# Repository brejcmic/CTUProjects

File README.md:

# CTUProjects
Student and research projects at CTU in Prag

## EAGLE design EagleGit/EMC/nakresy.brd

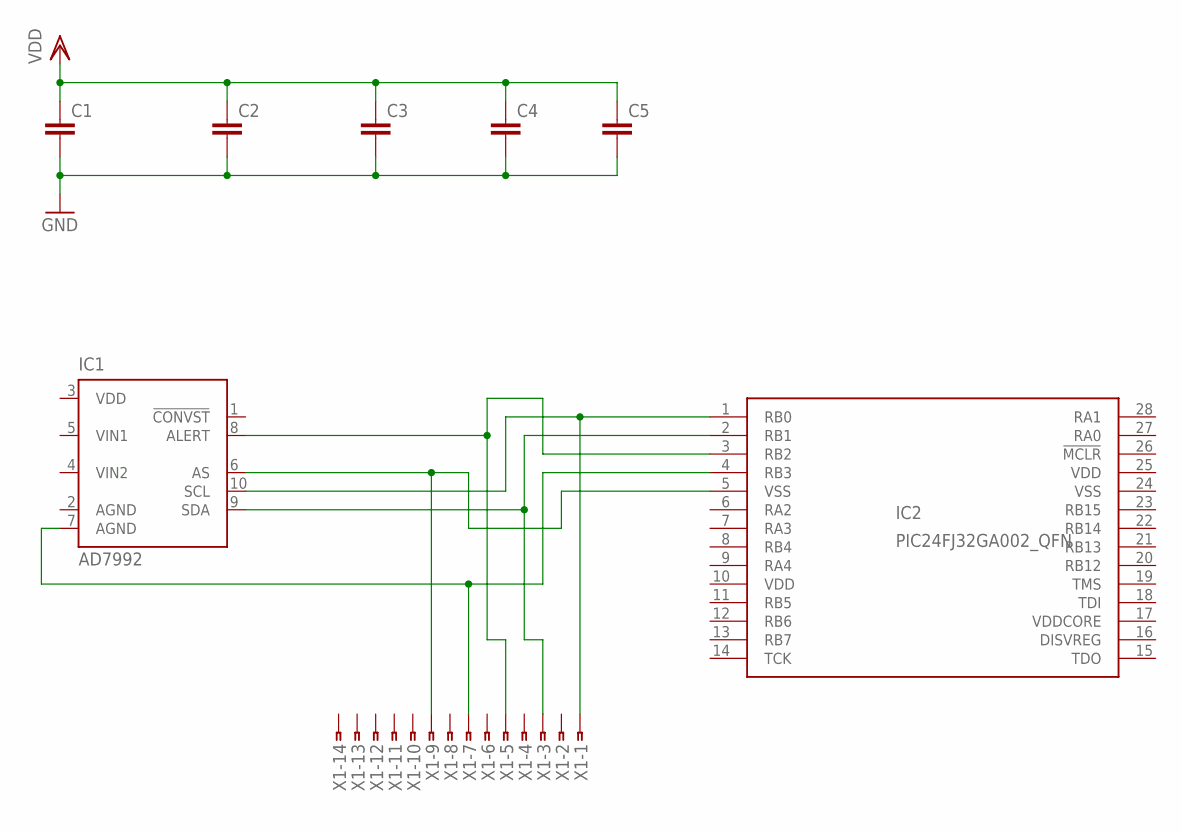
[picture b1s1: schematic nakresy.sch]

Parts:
C1, C2, C3, C4, C5: C-EUC0805K; C0805K
IC1: AD7992; MSOP10
IC2: PIC24FJ32GA002_QFN; QFN28-ML_6X6MM
X1: SMDTOP-14; SMDTOP14

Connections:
AGND: IC1.2 (AGND)
GND: C1.2, C2.2, C3.2, C4.2, C5.2
unnamed: IC1.10 (SCL), IC2.1 (RB0), X1.1
unnamed: IC1.9 (SDA), IC2.2 (RB1), X1.3
unnamed: IC1.8 (ALERT), IC2.3 (RB2), X1.5
unnamed: IC1.7 (AGND), IC2.4 (RB3), X1.7
unnamed: IC1.6 (AS), IC2.5 (VSS), X1.9
VDD: C1.1, C2.1, C3.1, C4.1, C5.1, IC1.3 (VDD), IC2.10 (VDD), IC2.25 (VDD)
VDDCORE: IC2.17 (VDDCORE)
VSS: IC2.24 (VSS)

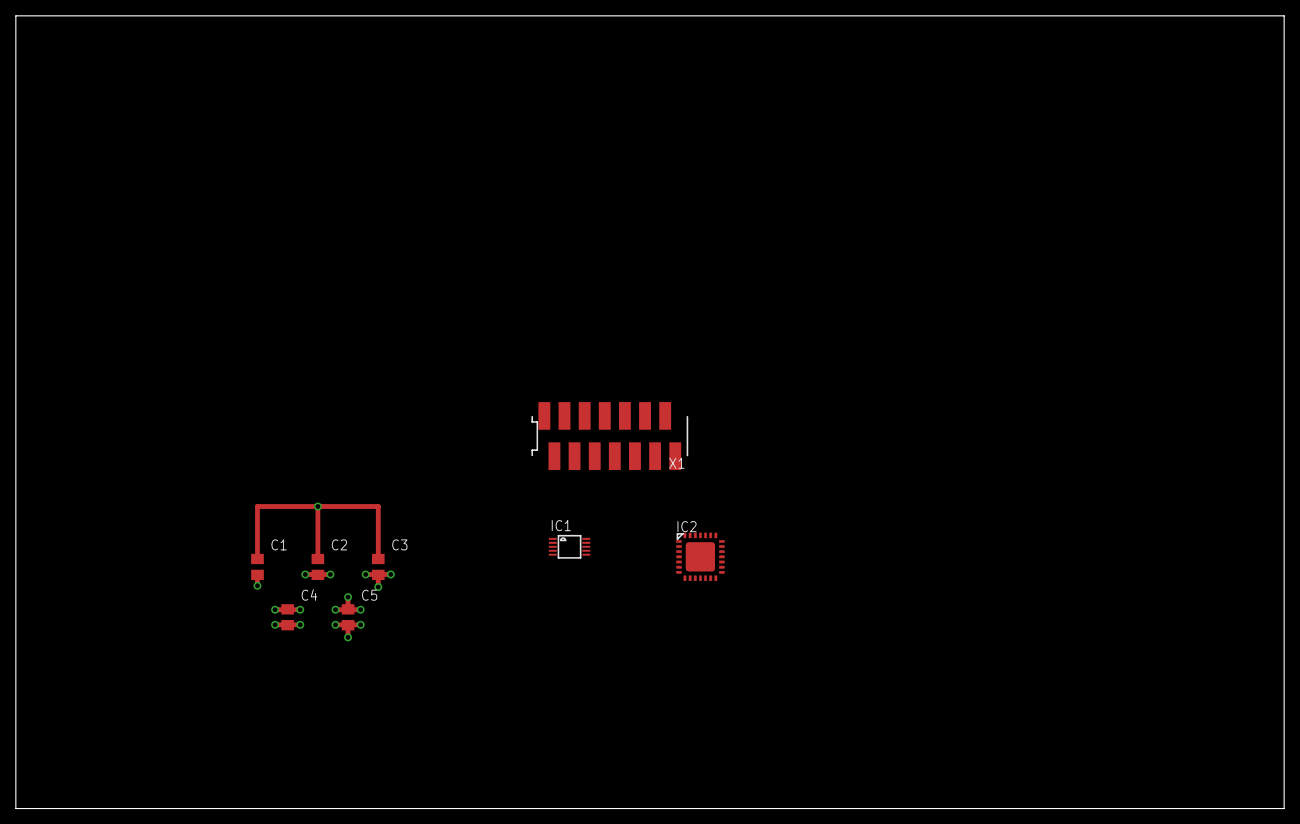
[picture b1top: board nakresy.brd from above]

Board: 4 copper layers, 160.0 x 100.0 mm, 8 parts (0 on the bottom side), 7 nets.

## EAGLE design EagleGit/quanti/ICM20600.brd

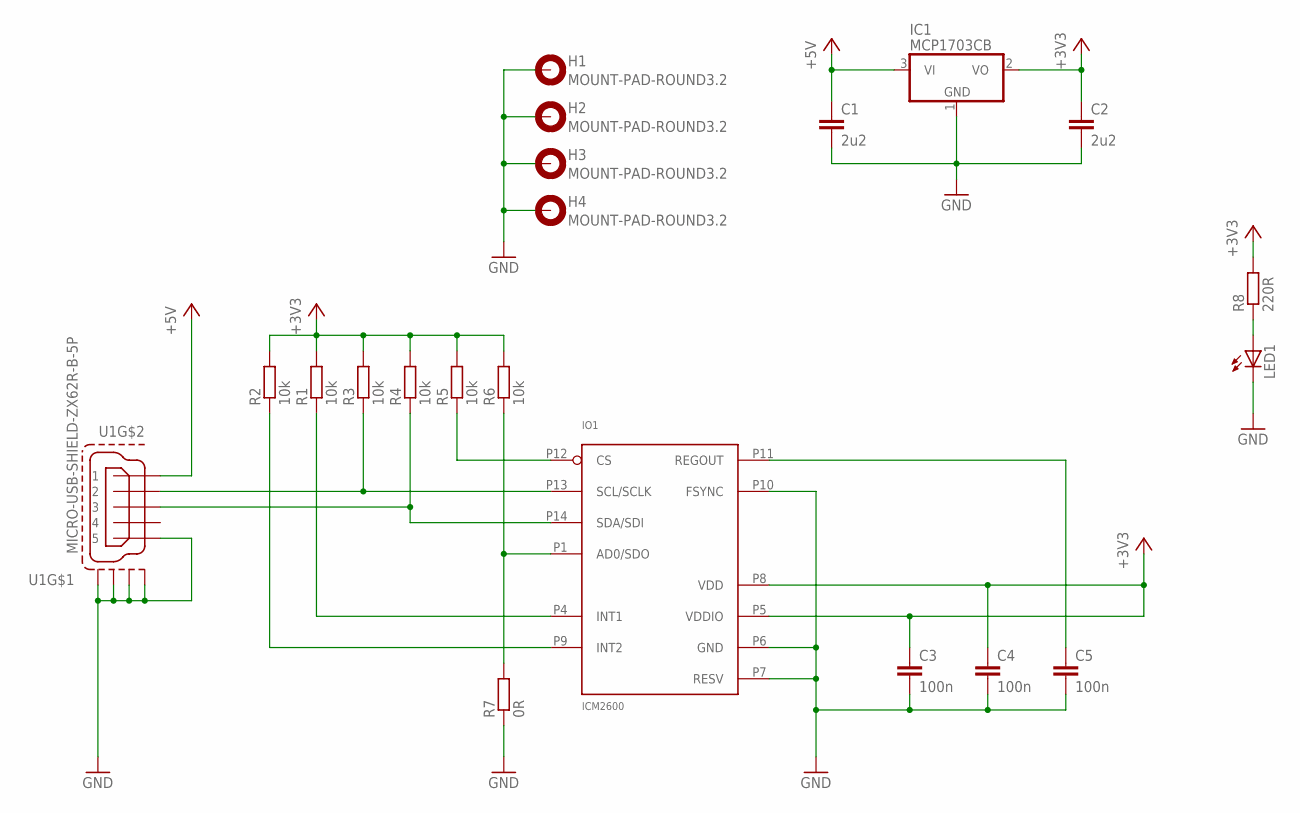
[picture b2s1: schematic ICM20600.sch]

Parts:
C1, C2: 2u2; C0603
C3, C4, C5: 100n; C0603
H1, H2, H3, H4: MOUNT-PAD-ROUND3.2; 3,2-PAD
IC1: MCP1703CB; SOT23
IO1: ICM2600; LGA14
LED1: LEDSML0603; SML0603
R1, R2, R3, R4, R5, R6: 10k; R0603
R7: 0R; R0603
R8: 220R; R0603
U1: MICRO-USB-SHIELD-ZX62R-B-5P; ZX62R-B-5P

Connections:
+3V3: C2.1, C3.1, C4.1, IC1.2 (VO), IO1.P5 (VDDIO), IO1.P8 (VDD), R1.2, R2.2, R3.2, R4.2, R5.2, R6.2, R8.2
+5V: C1.1, IC1.3 (VI), U1.1
GND: C1.2, C2.2, C3.2, C4.2, C5.2, H1.B3,2, H2.B3,2, H3.B3,2, H4.B3,2, IC1.1 (GND), IO1.P6 (GND), IO1.P7 (RESV), IO1.P10 (FSYNC), LED1.C, R7.1, U1.5, U1.M1 (S1), U1.M2 (S2), U1.M3 (S3), U1.M4 (S4)
unnamed: IO1.P9 (INT2), R2.1
unnamed: IO1.P4 (INT1), R1.1
unnamed: C5.1, IO1.P11 (REGOUT)
unnamed: IO1.P13 (SCL/SCLK), R3.1, U1.2
unnamed: IO1.P14 (SDA/SDI), R4.1, U1.3
unnamed: IO1.P12 (CS), R5.1
unnamed: IO1.P1 (AD0/SDO), R6.1, R7.2
unnamed: LED1.A, R8.1

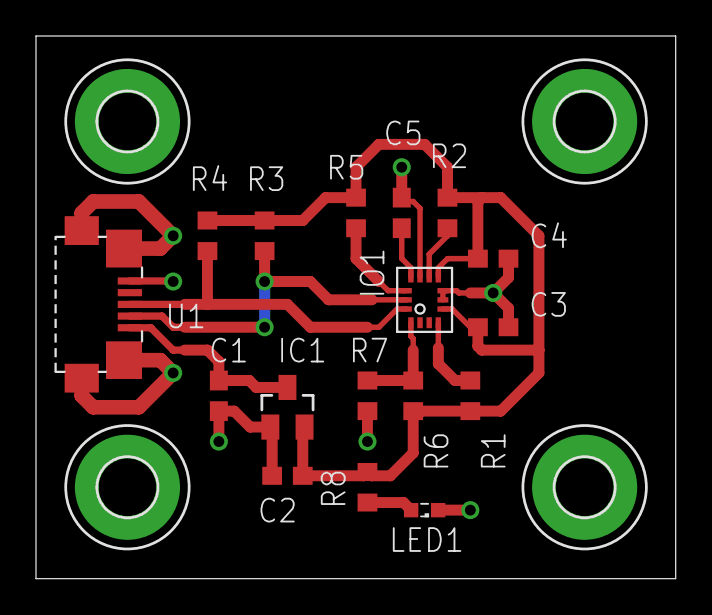
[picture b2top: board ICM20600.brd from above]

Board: 2 copper layers, 35.5 x 30.1 mm, 21 parts (0 on the bottom side), 11 nets.

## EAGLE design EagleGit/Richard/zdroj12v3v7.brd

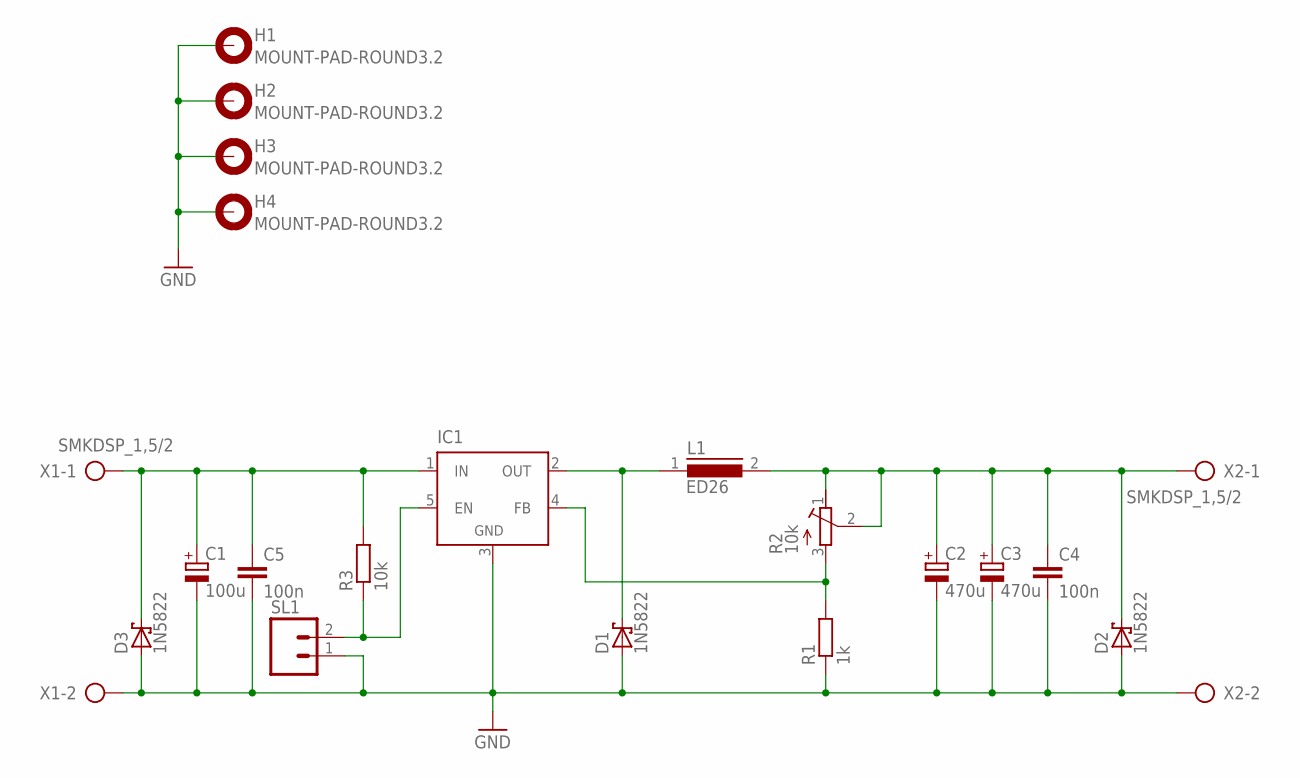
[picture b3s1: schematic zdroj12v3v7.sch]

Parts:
C1: 100u; E5-8,5
C2, C3: 470u; E5-10,5
C4, C5: 100n; C050-035X075
D1, D2, D3: 1N5822; DO201T15
H1, H2, H3, H4: MOUNT-PAD-ROUND3.2; 3,2-PAD
IC1: LM2596TH; TO220-52
L1: ED26
R1: 1k; 0207/10
R2: 10k; RTRIM3006P
R3: 10k; 0207/10
SL1: M02; 02P
X1, X2: SMKDSP_1,5/2

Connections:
GND: C1.-, C2.-, C3.-, C4.2, C5.2, D1.A, D2.A, D3.A, H1.B3,2, H2.B3,2, H3.B3,2, H4.B3,2, IC1.3 (GND), R1.1, SL1.1, X1.2, X2.2
unnamed: D1.C, IC1.2 (OUT), L1.1
unnamed: C2.+, C3.+, C4.1, D2.C, L1.2, R2.1 (E), R2.2 (S), X2.1
unnamed: IC1.4 (FB), R1.2, R2.3 (A)
unnamed: IC1.5 (EN), R3.1, SL1.2
unnamed: C1.+, C5.1, D3.C, IC1.1 (IN), R3.2, X1.1

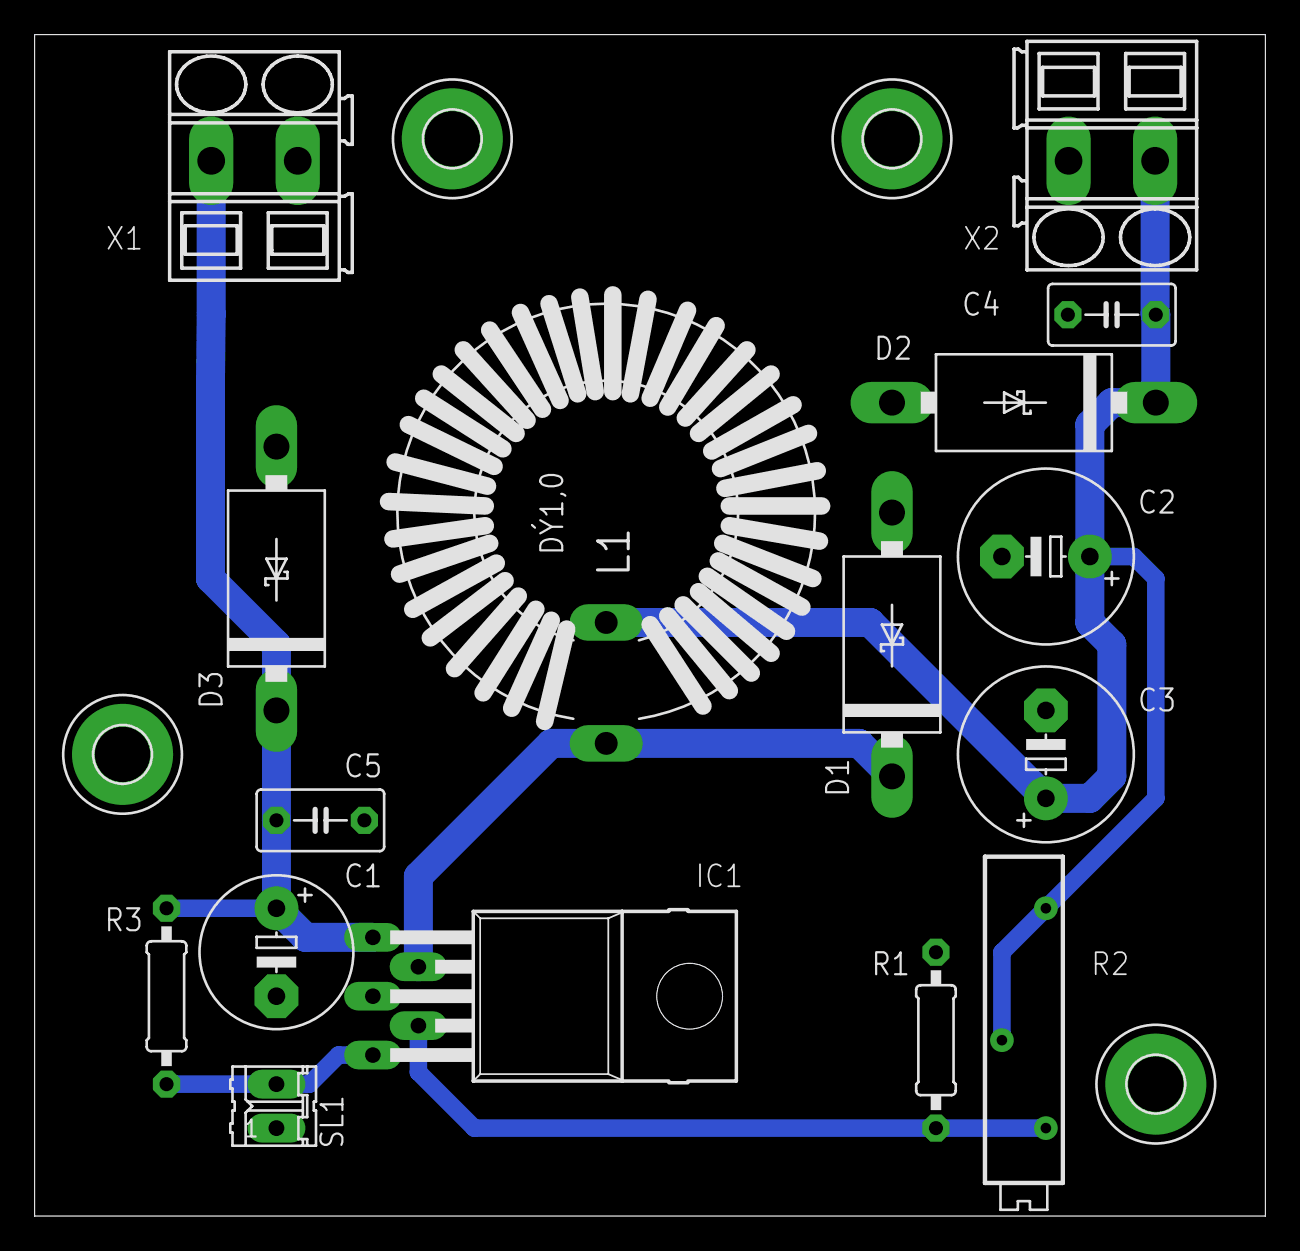
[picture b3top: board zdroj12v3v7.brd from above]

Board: 2 copper layers, 71.1 x 68.2 mm, 20 parts (0 on the bottom side), 6 nets.

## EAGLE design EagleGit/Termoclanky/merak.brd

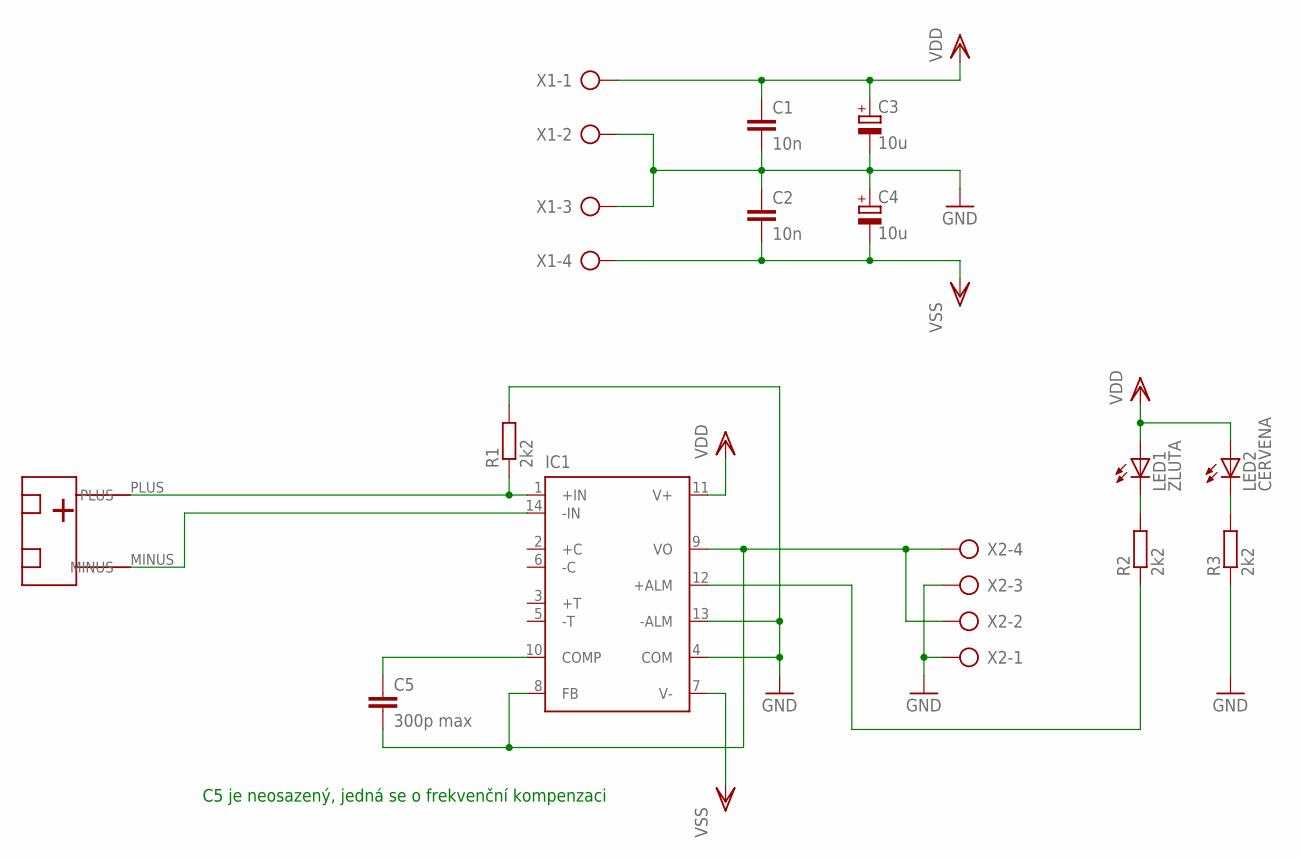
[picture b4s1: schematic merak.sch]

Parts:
C1, C2: 10n; C0805
C3, C4: 10u; E2,5-5
C5: 300p max; C0805
IC1: AD595; DIL14
LED1: ZLUTA; LED3MM
LED2: CERVENA; LED3MM
R1, R2, R3: 2k2; R0805
U$1: TERM_ZAS
X1, X2: AK300/4

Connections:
GND: C1.2, C2.1, C3.-, C4.+, IC1.4 (COM), IC1.13 (-ALM), R1.2, R3.1, X1.2, X1.3, X2.1, X2.3
MINUS: IC1.14 (-IN), U$1.MINUS
unnamed: C5.2, IC1.8 (FB), IC1.9 (VO), X2.2, X2.4
unnamed: C5.1, IC1.10 (COMP)
unnamed: LED1.K (C), R2.2
unnamed: LED2.K (C), R3.2
unnamed: IC1.12 (+ALM), R2.1
PLUS: IC1.1 (+IN), R1.1, U$1.PLUS
VDD: C1.1, C3.+, IC1.11 (V+), LED1.A, LED2.A, X1.1
VSS: C2.2, C4.-, IC1.7 (V-), X1.4

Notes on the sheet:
C5 je neosazený, jedná se o frekvenční kompenzaci

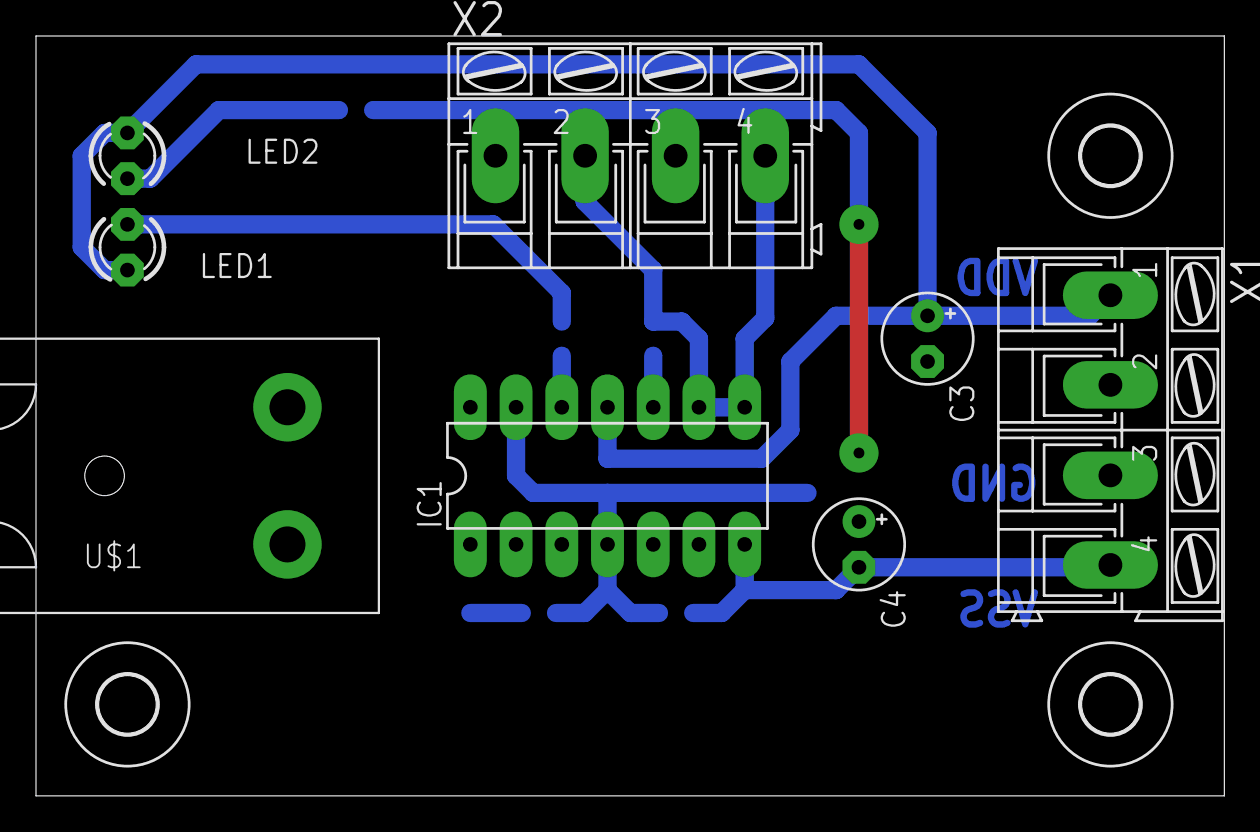
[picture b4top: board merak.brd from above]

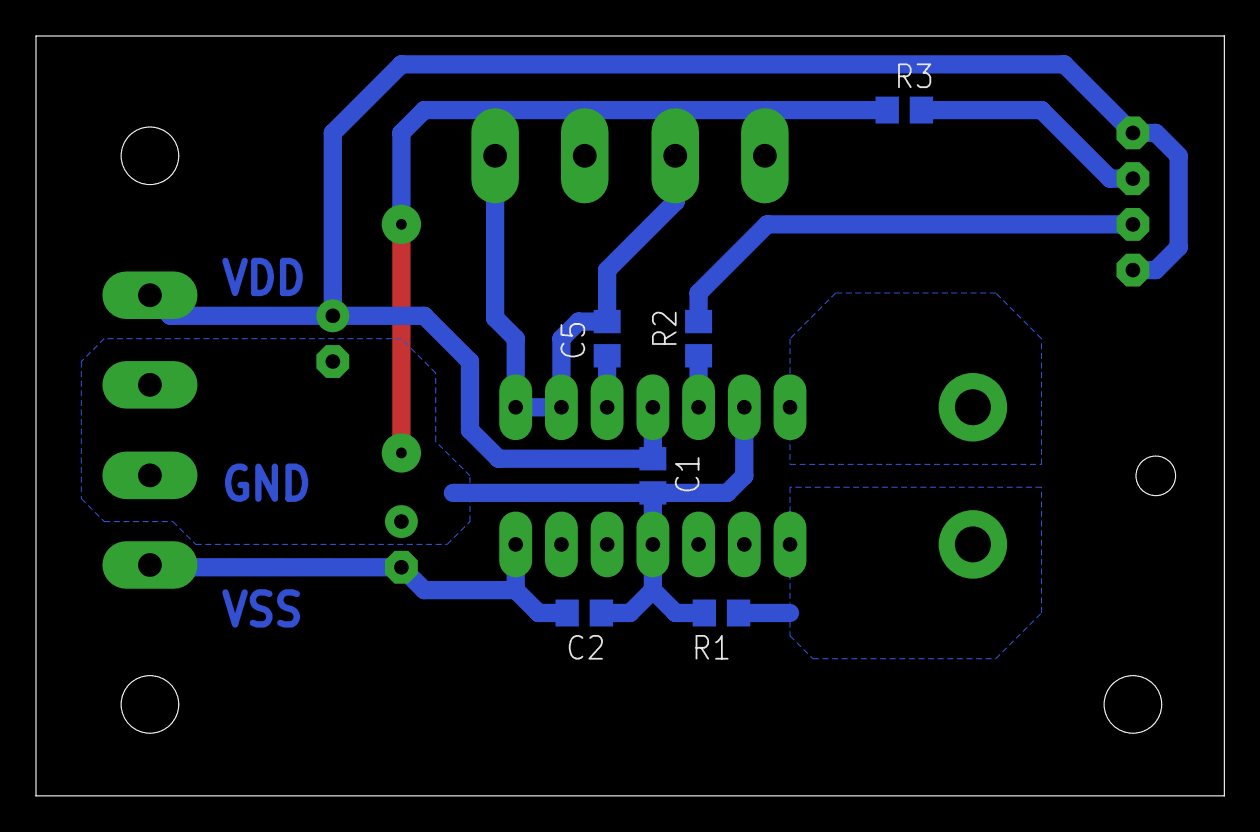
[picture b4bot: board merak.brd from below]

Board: 2 copper layers, 66.0 x 42.2 mm, 17 parts (6 on the bottom side), 10 nets.

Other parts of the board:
U$2, U$3, U$4: 3,2

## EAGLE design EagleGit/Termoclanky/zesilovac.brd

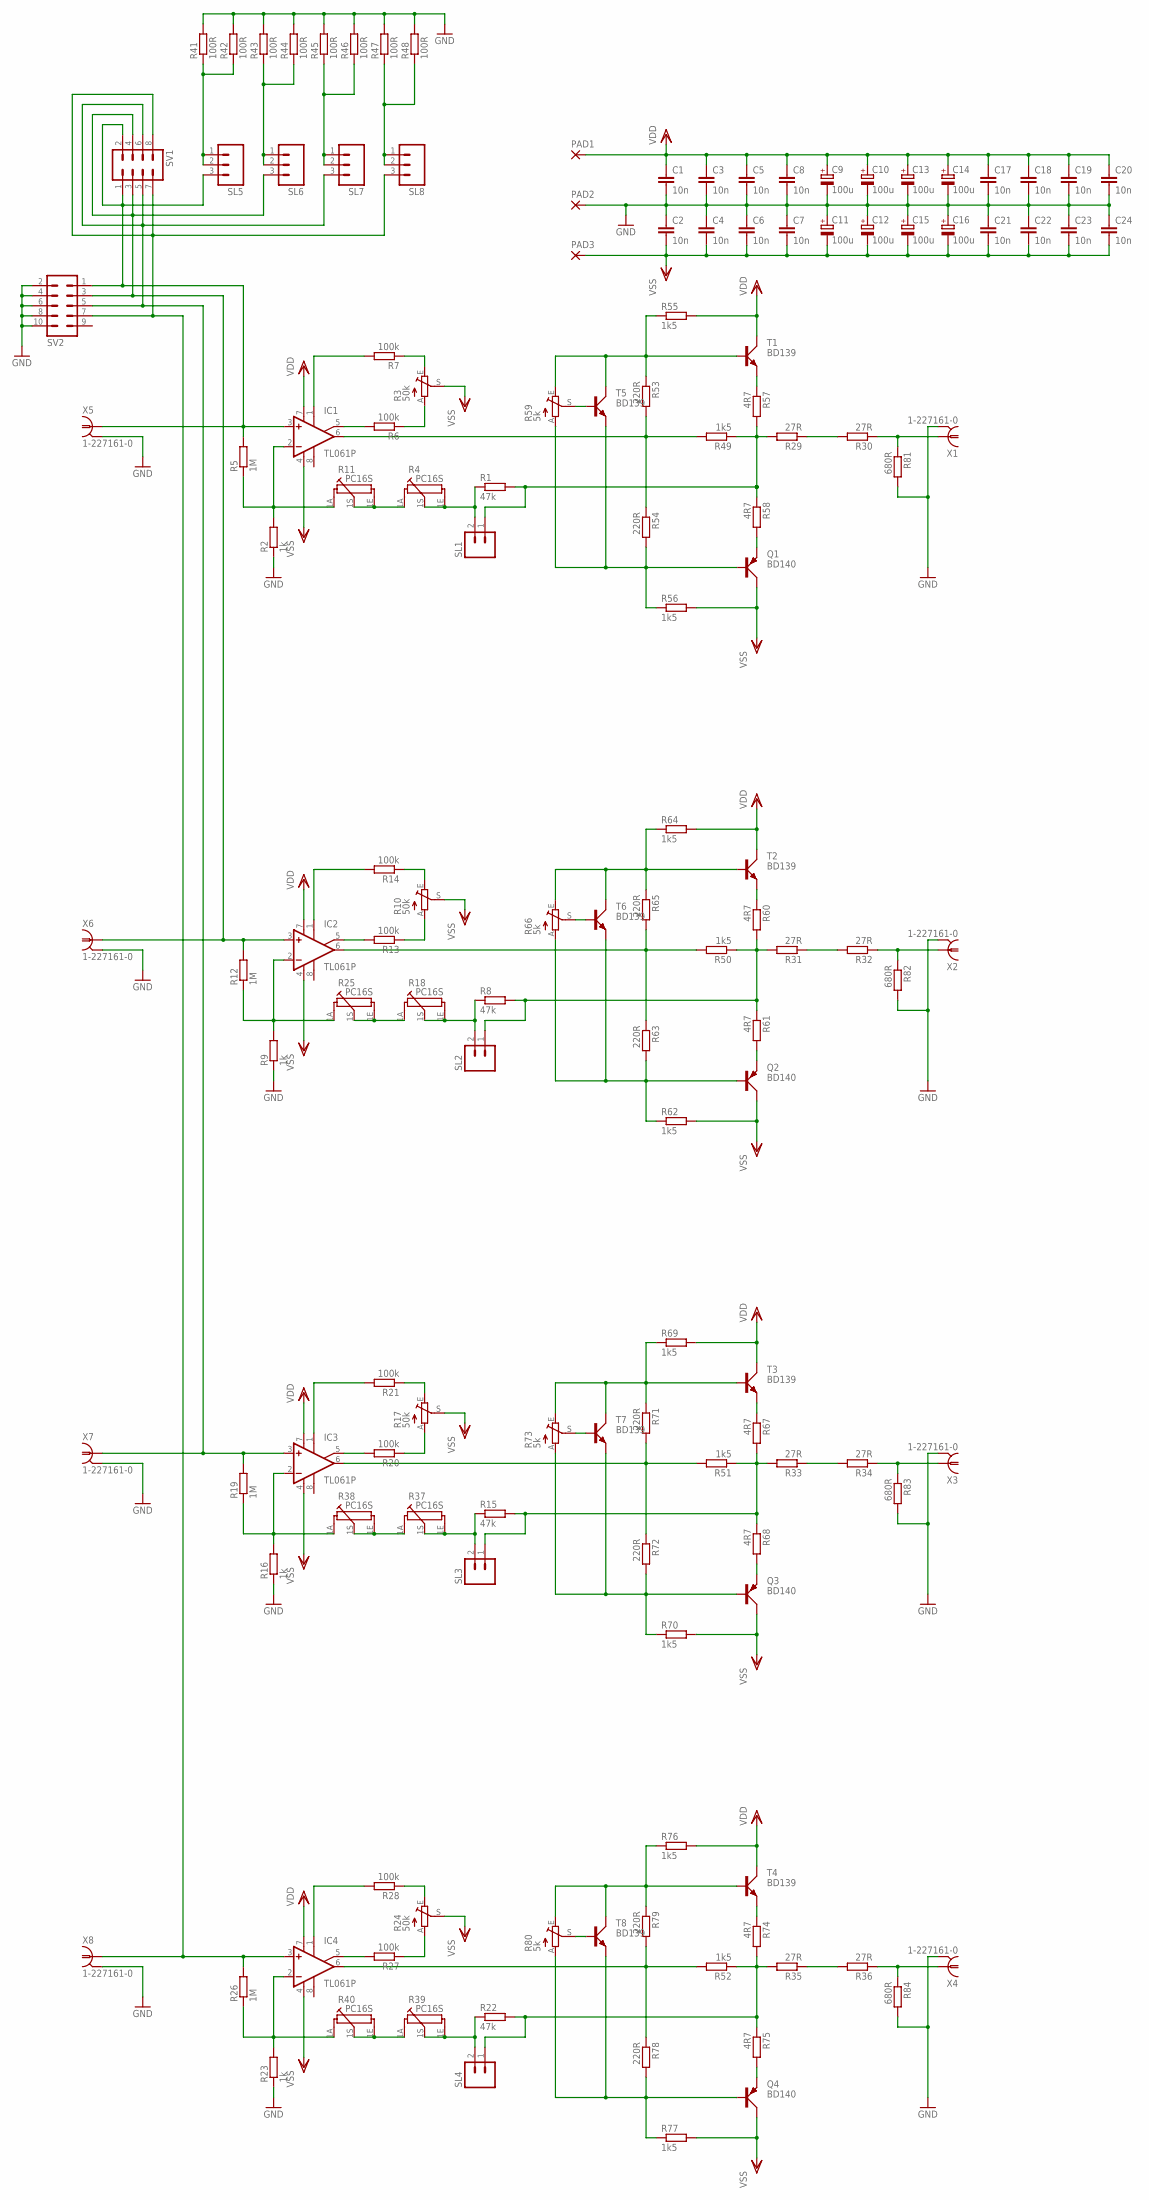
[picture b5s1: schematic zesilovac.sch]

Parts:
C1, C2, C3, C4, C5, C6, C7, C8, C17, C18, C19, C20, C21, C22, C23, C24: 10n; C5B5
C9, C10, C11, C12, C13, C14, C15, C16: 100u; E5-13
IC1, IC2, IC3, IC4: TL061P; DIL08
PAD1, PAD2, PAD3: 3,81/1,4
Q1, Q2, Q3, Q4: BD140; TO126AV
R1, R8, R15, R22: 47k; 0207/12
R2, R9, R16, R23: 1k; 0207/12
R3, R10, R17, R24: 50k; LI10
R4, R11, R18, R25, R37, R38, R39, R40: PC16S
R5, R12, R19, R26: 1M; 0207/12
R6, R7, R13, R14, R20, R21, R27, R28: 100k; 0207/12
R29, R30, R31, R32, R33, R34, R35, R36: 27R; 0411/12
R41, R42, R43, R44, R45, R46, R47, R48: 100R; 0207/12
R49, R50, R51, R52, R55, R56, R62, R64, R69, R70, R76, R77: 1k5; 0207/12
R53, R54, R63, R65, R71, R72, R78, R79: 220R; 0207/12
R57, R58, R60, R61, R67, R68, R74, R75: 4R7; 0207/12
R59, R66, R73, R80: 5k; LI10
R81, R82, R83, R84: 680R; 0207/12
SL1, SL2, SL3, SL4: M02; 02P
SL5, SL6, SL7, SL8: M03; 03P
SV1: MA04-2
SV2: MA05-2
T1, T2, T3, T4, T5, T6, T7, T8: BD139; TO126AV
X1, X2, X3, X4, X5, X6, X7, X8: 1-227161-0; AMP_227161

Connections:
GND: C1.2, C2.1, C3.2, C4.1, C5.2, C6.1, C7.1, C8.2, C9.-, C10.-, C11.+, C12.+, C13.-, C14.-, C15.+, C16.+, C17.2, C18.2, C19.2, C20.2, C21.1, C22.1, C23.1, C24.1, PAD2.1, R2.1, R9.1, R16.1, R23.1, R41.2, R42.2, R43.2, R44.2, R45.2, R46.2, R47.2, R48.2, R81.2, R82.2, R83.2, R84.2, SV2.2, SV2.4, SV2.6, SV2.8, SV2.10, X1.2, X2.2, X3.2, X4.2, X5.2, X6.2, X7.2, X8.2
unnamed: IC1.2 (-IN), R2.2, R5.1, R11.1A
unnamed: R1.1, R4.1E, R4.1S, SL1.2
unnamed: IC1.6 (OUT), R49.2, R53.2, R54.1
unnamed: IC1.1 (ON1), R7.2
unnamed: R3.A, R6.1
unnamed: IC1.3 (+IN), R5.2, SL5.3, SV1.1, SV1.2, SV2.1, X5.1
unnamed: R3.E, R7.1
unnamed: IC1.5 (ON2), R6.2
unnamed: IC2.2 (-IN), R9.2, R12.1, R25.1A
unnamed: R22.2, R35.2, R52.1, R74.2, R75.1, SL4.1
unnamed: IC2.1 (ON1), R14.2
unnamed: R10.A, R13.1
unnamed: R4.1A, R11.1E, R11.1S
unnamed: IC2.3 (+IN), R12.2, SL6.3, SV1.3, SV1.4, SV2.3, X6.1
unnamed: R10.E, R14.1
unnamed: IC2.5 (ON2), R13.2
unnamed: IC3.2 (-IN), R16.2, R19.1, R38.1A
unnamed: R15.2, R33.2, R51.1, R67.2, R68.1, SL3.1
unnamed: IC3.1 (ON1), R21.2
unnamed: R17.A, R20.1
unnamed: R15.1, R37.1E, R37.1S, SL3.2
unnamed: IC3.3 (+IN), R19.2, SL7.3, SV1.5, SV1.6, SV2.5, X7.1
unnamed: R17.E, R21.1
unnamed: IC3.5 (ON2), R20.2
unnamed: IC4.2 (-IN), R23.2, R26.1, R40.1A
unnamed: R8.2, R31.2, R50.1, R60.2, R61.1, SL2.1
unnamed: IC4.1 (ON1), R28.2
unnamed: R24.A, R27.1
unnamed: R22.1, R39.1E, R39.1S, SL4.2
unnamed: IC4.3 (+IN), R26.2, SL8.3, SV1.7, SV1.8, SV2.7, X8.1
unnamed: R24.E, R28.1
unnamed: IC4.5 (ON2), R27.2
unnamed: R8.1, R18.1E, R18.1S, SL2.2
unnamed: R18.1A, R25.1E, R25.1S
unnamed: R37.1A, R38.1E, R38.1S
unnamed: R29.1, R30.2
unnamed: R31.1, R32.2
unnamed: R35.1, R36.2
unnamed: R36.1, R84.1, X4.1
unnamed: R39.1A, R40.1E, R40.1S
unnamed: Q1.B, R54.2, R56.1, R59.A, T5.E
unnamed: R43.1, R44.1, SL6.1, SL6.2
unnamed: R45.1, R46.1, SL7.1, SL7.2
unnamed: R47.1, R48.1, SL8.1, SL8.2
unnamed: IC2.6 (OUT), R50.2, R63.1, R65.2
unnamed: R1.2, R29.2, R49.1, R57.2, R58.1, SL1.1
unnamed: R41.1, R42.1, SL5.1, SL5.2
unnamed: IC3.6 (OUT), R51.2, R71.2, R72.1
unnamed: R53.1, R55.1, R59.E, T1.B, T5.C
unnamed: IC4.6 (OUT), R52.2, R78.1, R79.2
unnamed: R57.1, T1.E
unnamed: Q1.E, R58.2
unnamed: R59.S, T5.B
unnamed: R67.1, T3.E
unnamed: Q2.E, R61.2
unnamed: Q3.E, R68.2
unnamed: R60.1, T2.E
unnamed: Q2.B, R62.1, R63.2, R66.A, T6.E
unnamed: R64.1, R65.1, R66.E, T2.B, T6.C
unnamed: R66.S, T6.B
unnamed: R69.1, R71.1, R73.E, T3.B, T7.C
unnamed: Q3.B, R70.1, R72.2, R73.A, T7.E
unnamed: R74.1, T4.E
unnamed: Q4.E, R75.2
unnamed: R73.S, T7.B
unnamed: R30.1, R81.1, X1.1
unnamed: R32.1, R82.1, X2.1
unnamed: R76.1, R79.1, R80.E, T4.B, T8.C
unnamed: Q4.B, R77.1, R78.2, R80.A, T8.E
unnamed: R80.S, T8.B
unnamed: R33.1, R34.2
unnamed: R34.1, R83.1, X3.1
VDD: C1.1, C3.1, C5.1, C8.1, C9.+, C10.+, C13.+, C14.+, C17.1, C18.1, C19.1, C20.1, IC1.7 (V+), IC2.7 (V+), IC3.7 (V+), IC4.7 (V+), PAD1.1, R55.2, R64.2, R69.2, R76.2, T1.C, T2.C, T3.C, T4.C
VSS: C2.2, C4.2, C6.2, C7.2, C11.-, C12.-, C15.-, C16.-, C21.2, C22.2, C23.2, C24.2, IC1.4 (V-), IC2.4 (V-), IC3.4 (V-), IC4.4 (V-), PAD3.1, Q1.C, Q2.C, Q3.C, Q4.C, R3.S, R10.S, R17.S, R24.S, R56.2, R62.2, R70.2, R77.2

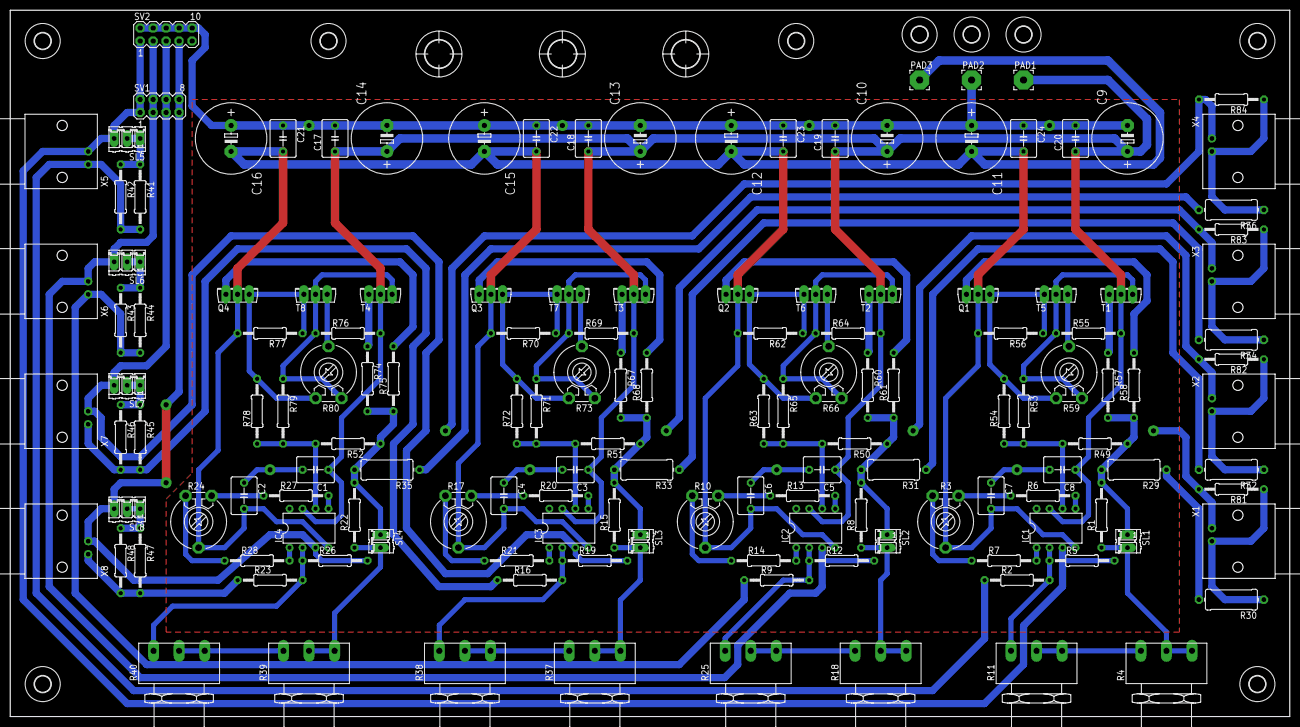
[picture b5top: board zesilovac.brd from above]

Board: 2 copper layers, 250.2 x 138.1 mm, 157 parts (0 on the bottom side), 75 nets.

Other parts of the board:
U$1, U$2, U$3, U$4, U$8, U$9, U$10, U$11, U$12: 3,2
U$5, U$6, U$7: 5,5

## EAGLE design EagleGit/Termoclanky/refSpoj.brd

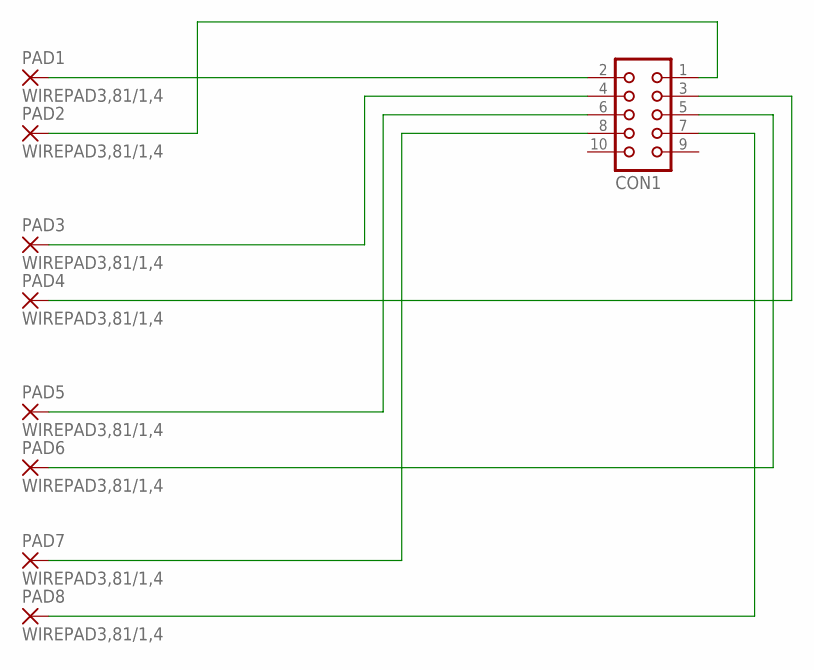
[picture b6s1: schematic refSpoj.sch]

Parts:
CON1: CON10
PAD1, PAD2, PAD3, PAD4, PAD5, PAD6, PAD7, PAD8: WIREPAD3,81/1,4; 3,81/1,4

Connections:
unnamed: CON1.2, PAD1.1
unnamed: CON1.1, PAD2.1
unnamed: CON1.4, PAD3.1
unnamed: CON1.3, PAD4.1
unnamed: CON1.6, PAD5.1
unnamed: CON1.5, PAD6.1
unnamed: CON1.8, PAD7.1
unnamed: CON1.7, PAD8.1

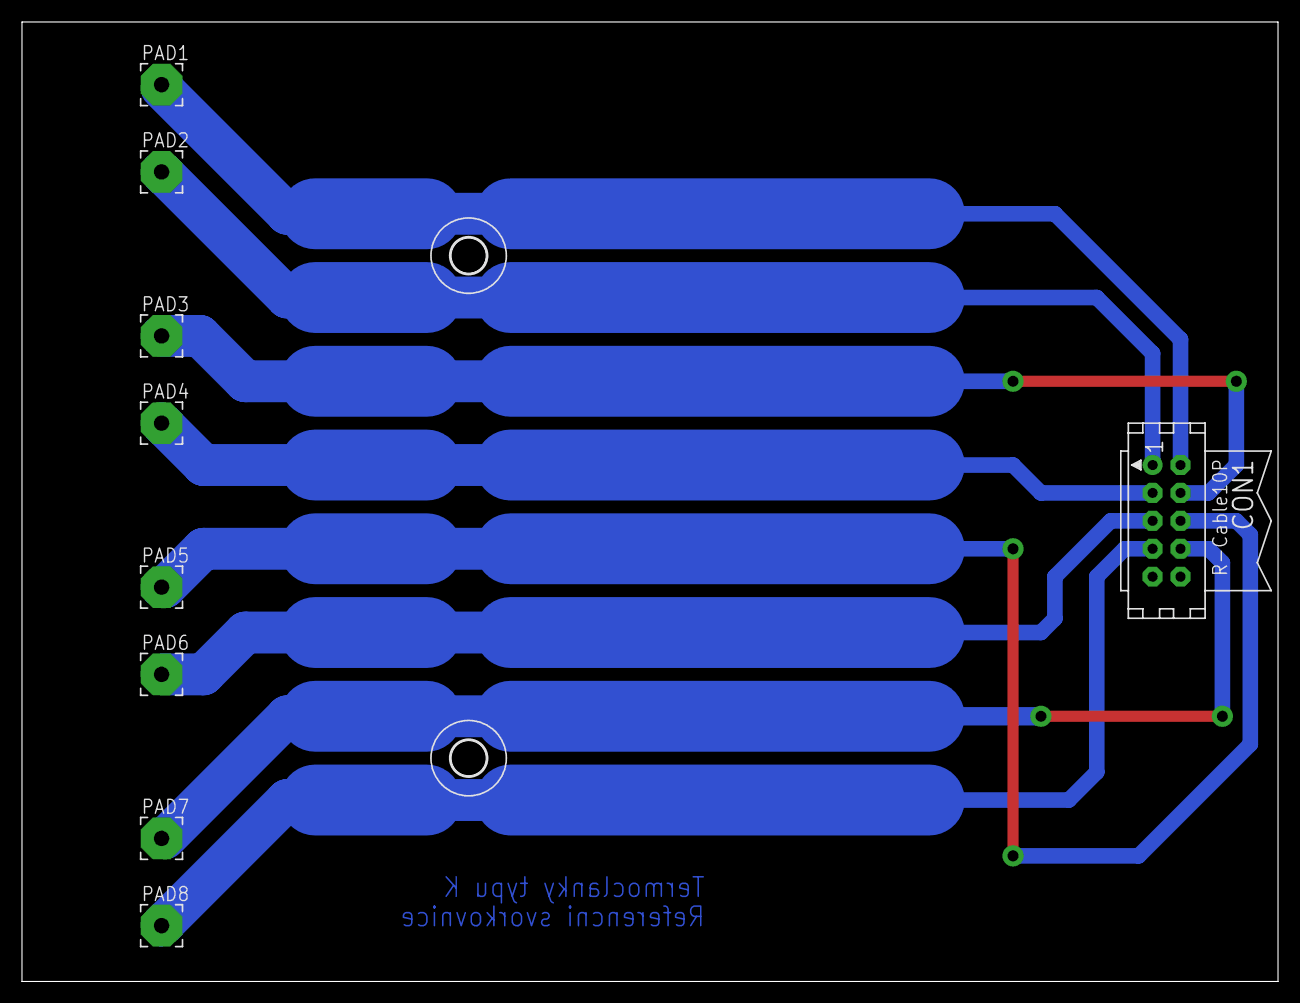
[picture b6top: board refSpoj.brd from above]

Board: 2 copper layers, 114.3 x 87.3 mm, 11 parts (0 on the bottom side), 8 nets.

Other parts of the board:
U$1, U$2: 3,2

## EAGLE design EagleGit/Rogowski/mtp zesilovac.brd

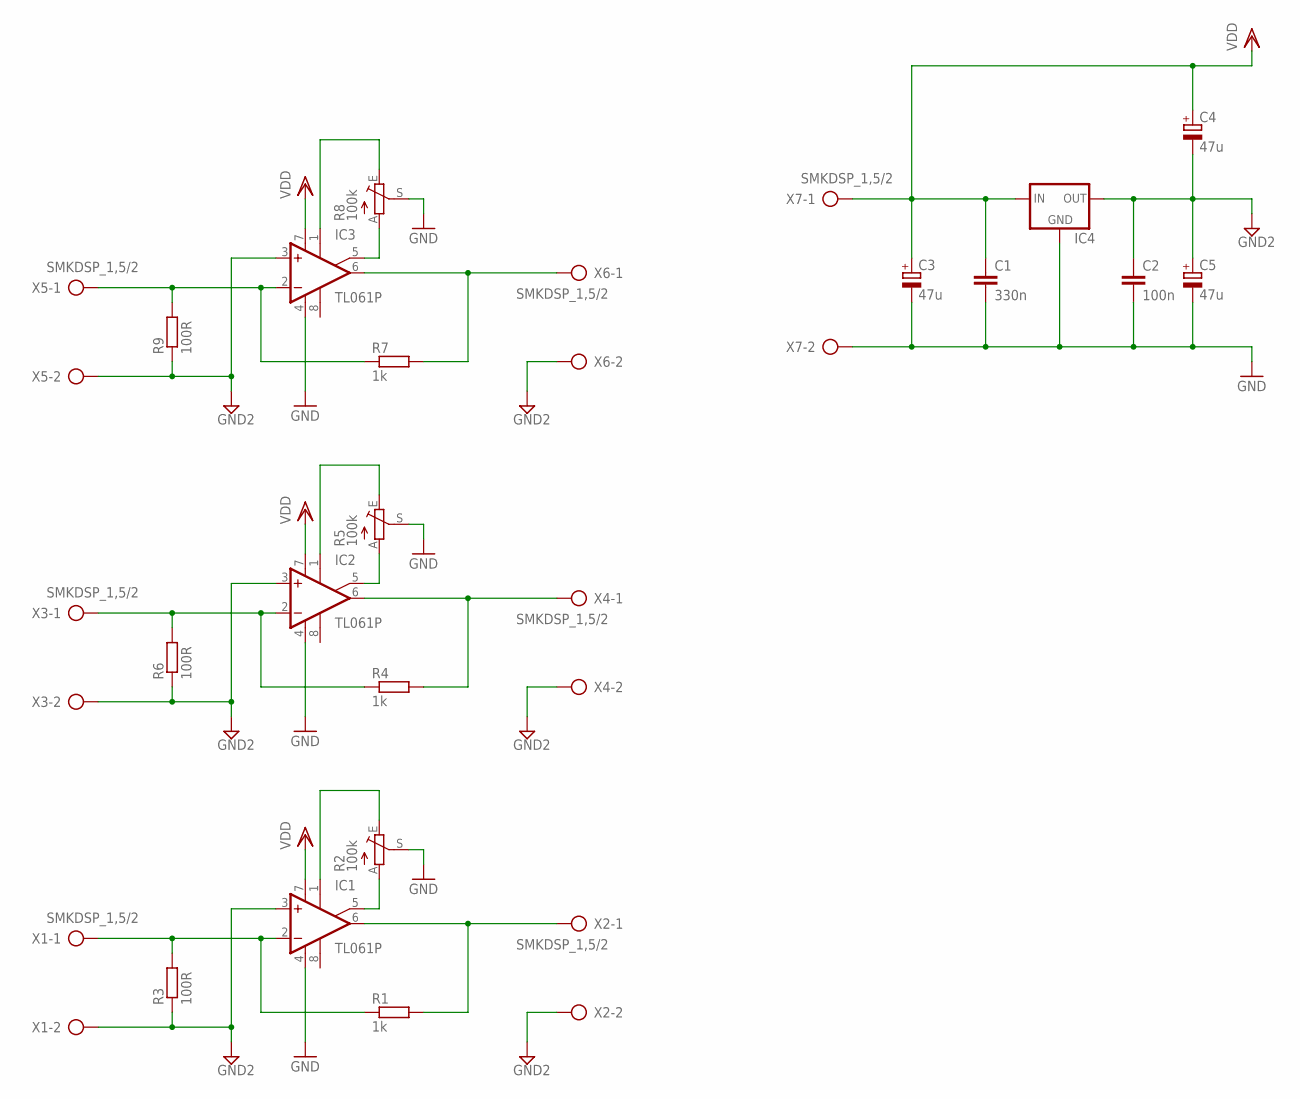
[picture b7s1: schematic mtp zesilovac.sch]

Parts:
C1: 330n; C050-045X075
C2: 100n; C050-045X075
C3, C4, C5: 47u; E2,5-7
IC1, IC2, IC3: TL061P; DIL08
IC4: 78LXX
R1, R4, R7: 1k; 0207/12
R2, R5, R8: 100k; LI10
R3, R6, R9: 100R; 0207/12
X1, X2, X3, X4, X5, X6, X7: SMKDSP_1,5/2

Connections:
GND: C1.2, C2.2, C3.-, C5.-, IC1.4 (V-), IC2.4 (V-), IC3.4 (V-), IC4.GND, R2.S, R5.S, R8.S, X7.2
GND2: C2.1, C4.-, C5.+, IC1.3 (+IN), IC2.3 (+IN), IC3.3 (+IN), IC4.OUT, R3.1, R6.1, R9.1, X1.2, X2.2, X3.2, X4.2, X5.2, X6.2
unnamed: IC1.2 (-IN), R1.1, R3.2, X1.1
unnamed: IC1.6 (OUT), R1.2, X2.1
unnamed: IC1.5 (ON2), R2.A
unnamed: IC1.1 (ON1), R2.E
unnamed: IC2.2 (-IN), R4.1, R6.2, X3.1
unnamed: IC2.6 (OUT), R4.2, X4.1
unnamed: IC2.5 (ON2), R5.A
unnamed: IC2.1 (ON1), R5.E
unnamed: IC3.2 (-IN), R7.1, R9.2, X5.1
unnamed: IC3.6 (OUT), R7.2, X6.1
unnamed: IC3.5 (ON2), R8.A
unnamed: IC3.1 (ON1), R8.E
VDD: C1.1, C3.+, C4.+, IC1.7 (V+), IC2.7 (V+), IC3.7 (V+), IC4.IN, X7.1

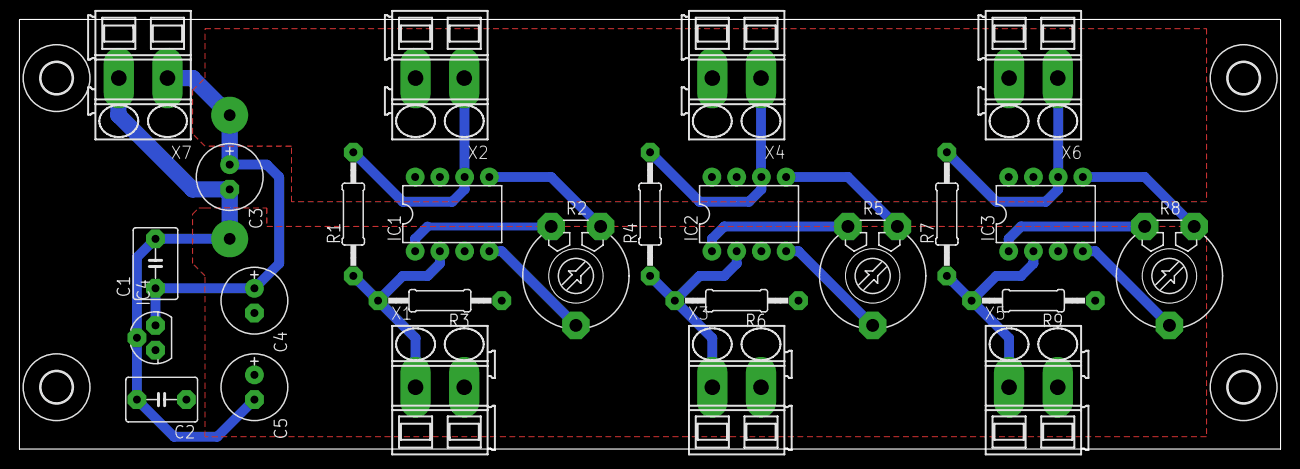
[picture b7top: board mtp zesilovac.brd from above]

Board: 2 copper layers, 129.5 x 44.1 mm, 29 parts (0 on the bottom side), 15 nets.

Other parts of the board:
U$1, U$2, U$3, U$4: 3,2
